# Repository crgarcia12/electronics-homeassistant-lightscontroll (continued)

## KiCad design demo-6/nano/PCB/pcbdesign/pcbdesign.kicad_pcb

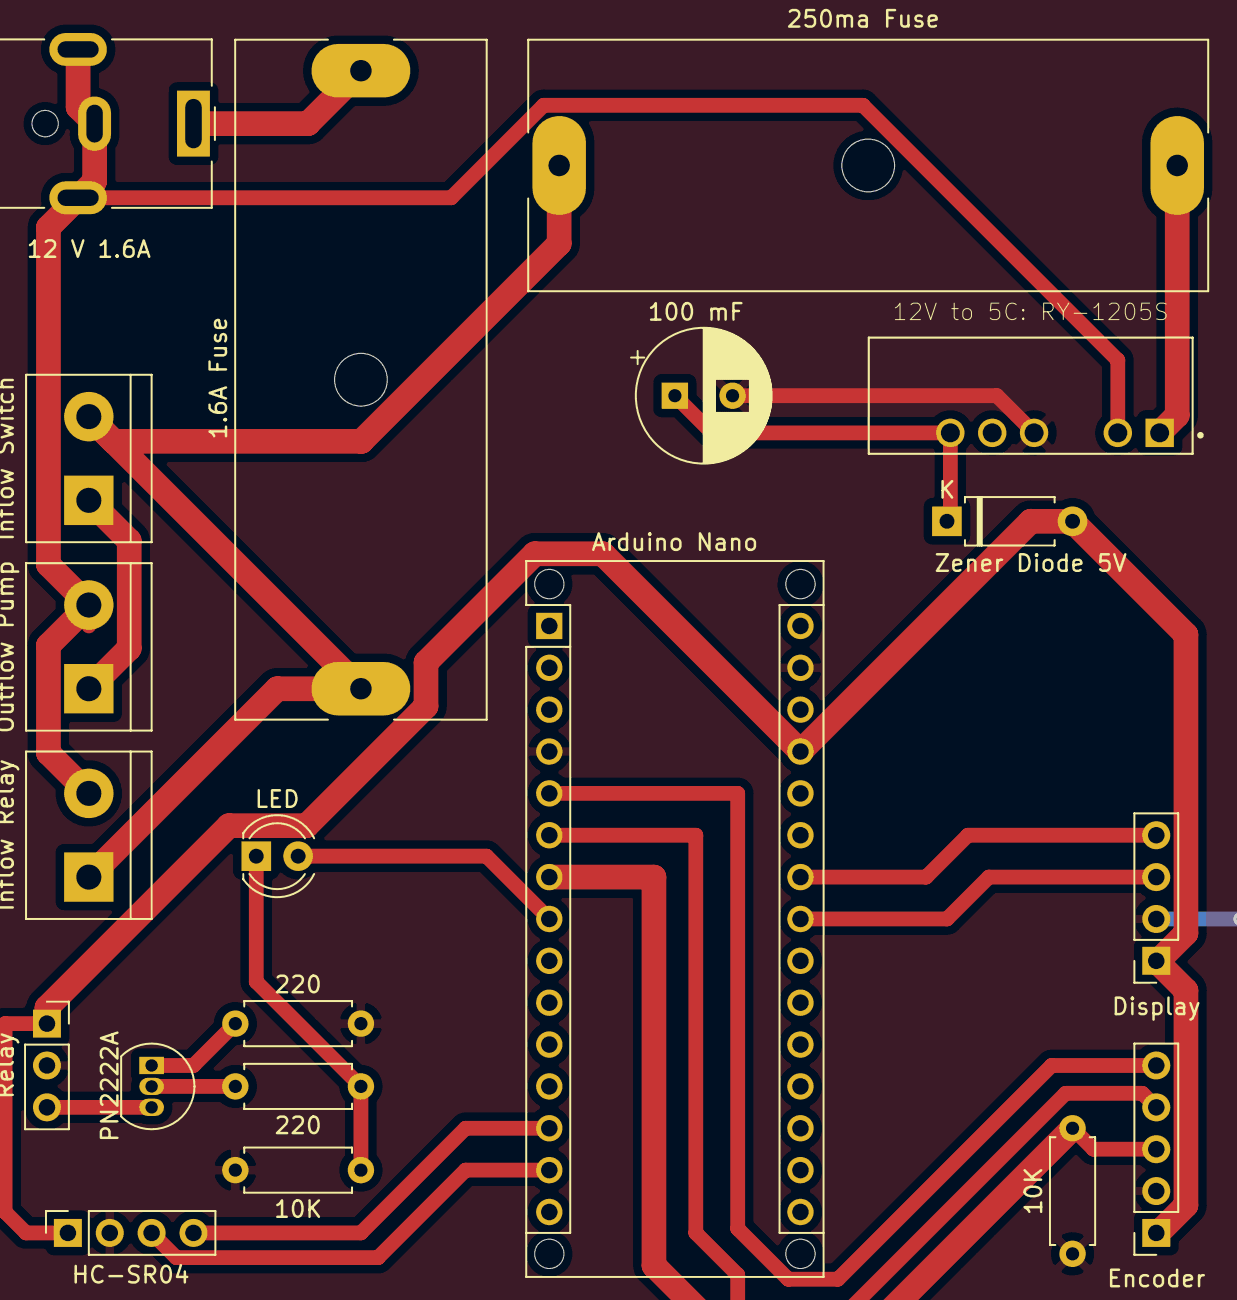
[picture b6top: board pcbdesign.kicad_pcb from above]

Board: 2 copper layers, 20 parts (0 on the bottom side), 20 nets.

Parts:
1.6A Fuse: 1.6A Fuse; Fuseholder_Cylinder-6.3x32mm_Schurter_0031-8002_Horizontal_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
10K, 10K#2: 10K; R_Axial_DIN0207_L6.3mm_D2.5mm_P7.62mm_Horizontal
12 V 1.6A: 12v input; BarrelJack_CUI_PJ-063AH_Horizontal
12V to 5C: RY-1205S: RY-1205S; CONV_RY-1205S
100 mF: 100 mF; CP_Radial_D8.0mm_P3.50mm
220, 220#2: 220; R_Axial_DIN0207_L6.3mm_D2.5mm_P7.62mm_Horizontal
250ma Fuse: 250ma Fuse; Fuseholder_Cylinder-6.3x32mm_Schurter_0031-8002_Horizontal_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
Arduino Nano: Arduino_Nano_v3.x; Arduino_Nano_WithMountingHoles
Display: Display; PinSocket_1x04_P2.54mm_Vertical
Encoder: Encoder; PinSocket_1x05_P2.54mm_Vertical
HC-SR04: HC-SR04; PinSocket_1x04_P2.54mm_Vertical
Inflow Relay: Inflow Relay; TerminalBlock_bornier-2_P5.08mm
Inflow Switch: Outflow Switch; TerminalBlock_bornier-2_P5.08mm
LED: LED; LED_D4.0mm
Outflow Pump: Outflow Pump; TerminalBlock_bornier-2_P5.08mm
PN2222A: PN2222A; TO-92_Inline
Relay: Relay; PinSocket_1x03_P2.54mm_Vertical
Zener Diode 5V: 5V; D_A-405_P7.62mm_Horizontal

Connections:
+5V: Arduino Nano.27, Display.1, Encoder.1, HC-SR04.1, Relay.1, Zener Diode 5V.2
GND: 10K.2, 10K#2.1, 12V to 5C: RY-1205S.4, 100 mF.2, 220#2.2, Arduino Nano.4, Arduino Nano.29, Display.2, Encoder.2, HC-SR04.2, Relay.2
unnamed: Arduino Nano.5, Encoder.5
unnamed: Arduino Nano.6, Encoder.4
unnamed: 10K#2.2, Arduino Nano.7, Encoder.3
unnamed: Arduino Nano.8, LED.2
unnamed: Arduino Nano.13, HC-SR04.4
unnamed: Arduino Nano.14, HC-SR04.3
unnamed: Arduino Nano.23, Display.3
unnamed: Arduino Nano.24, Display.4
unnamed: 12V to 5C: RY-1205S.6, 100 mF.1, Zener Diode 5V.1
unnamed: 10K.1, 220.1, LED.1
unnamed: 1.6A Fuse.1, 250ma Fuse.2, Inflow Relay.1, Inflow Switch.2
unnamed: 1.6A Fuse.2, 12 V 1.6A.1
unnamed: 12V to 5C: RY-1205S.1, 250ma Fuse.1
unnamed: PN2222A.3, Relay.3
unnamed: 12 V 1.6A.2, 12 V 1.6A.MP, 12V to 5C: RY-1205S.2, Inflow Relay.2, Outflow Pump.2
unnamed: Inflow Switch.1, Outflow Pump.1
unnamed: 220#2.1, PN2222A.1
unnamed: 220.2, PN2222A.2

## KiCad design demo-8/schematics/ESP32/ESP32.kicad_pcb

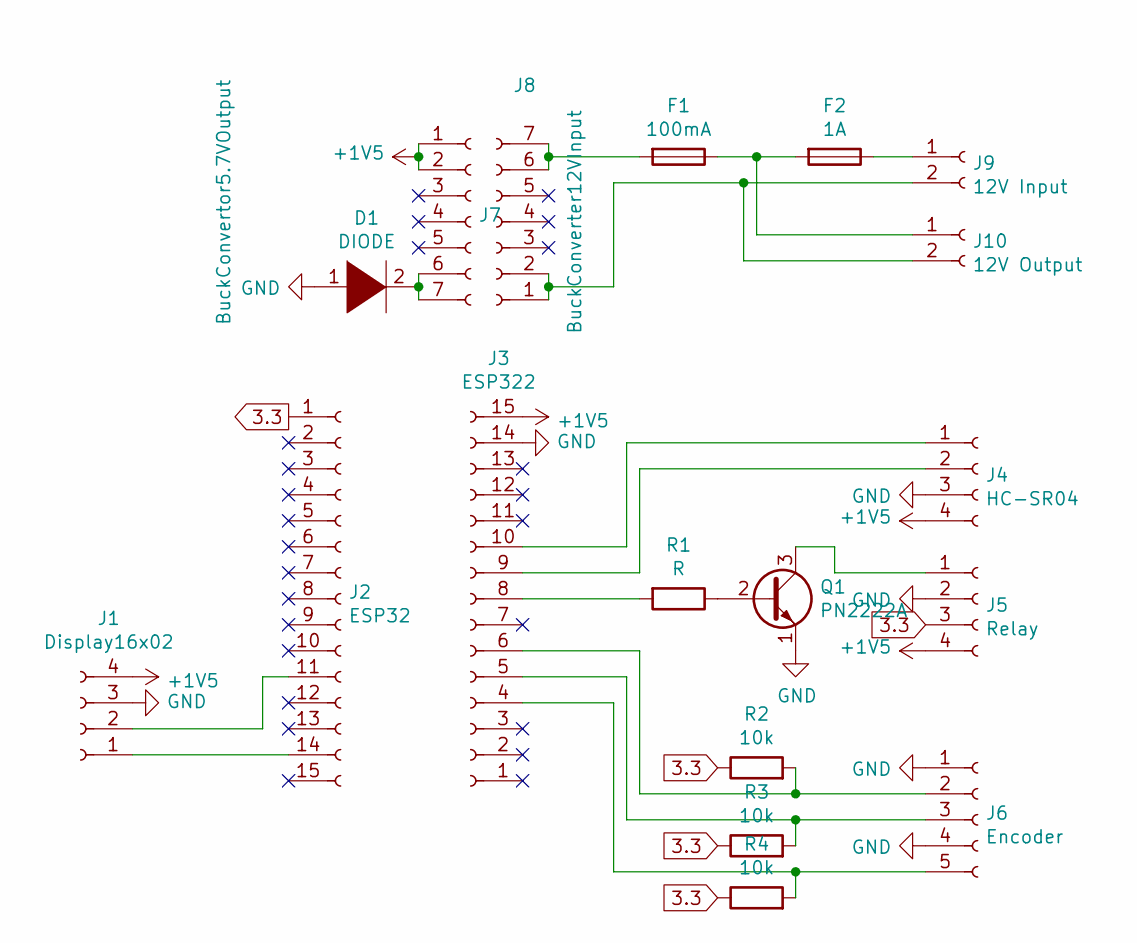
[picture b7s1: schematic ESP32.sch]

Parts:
D1: DIODE; D_5W_P12.70mm_Horizontal
F1: 100mA; Fuse_BelFuse_0ZRE0150FF_L23.4mm_W5.3mm
F2: 1A; Fuse_BelFuse_0ZRE0150FF_L23.4mm_W5.3mm
J1: Display16x02; PinSocket_1x04_P1.00mm_Vertical
J2: ESP32; PinSocket_1x15_P1.00mm_Vertical
J3: ESP322; PinSocket_1x15_P1.00mm_Vertical
J4: HC-SR04; PinSocket_1x04_P1.00mm_Vertical
J5: Relay; PinSocket_1x04_P1.00mm_Vertical
J6: Encoder; PinSocket_1x05_P1.00mm_Vertical
J7: BuckConvertor5.7VOutput; PinHeader_1x07_P1.00mm_Vertical
J8: BuckConverter12VInput; PinHeader_1x07_P1.00mm_Vertical
J9: 12V Input; PhoenixContact_GMSTBVA_2,5_2-G-7,62_1x02_P7.62mm_Vertical
J10: 12V Output; PhoenixContact_GMSTBVA_2,5_2-G-7,62_1x02_P7.62mm_Vertical
Q1: PN2222A; TO-92_Inline
R1: R; R_Axial_DIN0204_L3.6mm_D1.6mm_P5.08mm_Horizontal
R2, R3, R4: 10k; R_Axial_DIN0204_L3.6mm_D1.6mm_P5.08mm_Horizontal

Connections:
3.3: J2.1, J5.3, R2.1, R3.1, R4.1
+1V5: J1.4, J3.15, J4.4, J5.4, J7.1, J7.2
GND: D1.1 (K), J1.3, J3.14, J4.3, J5.2, J6.1, J6.4, Q1.1 (E)
unnamed: D1.2 (A), J7.6, J7.7
unnamed: F1.1, F2.2, J10.1
unnamed: F1.2, J8.6, J8.7
unnamed: F2.1, J9.1
unnamed: J1.1, J2.14
unnamed: J1.2, J2.11
unnamed: J3.4, J6.5, R4.2
unnamed: J3.5, J6.3, R3.2
unnamed: J3.6, J6.2, R2.2
unnamed: J3.8, R1.2
unnamed: J3.9, J4.2
unnamed: J3.10, J4.1
unnamed: J5.1, Q1.3 (C)
unnamed: J8.1, J8.2, J9.2, J10.2
unnamed: Q1.2 (B), R1.1

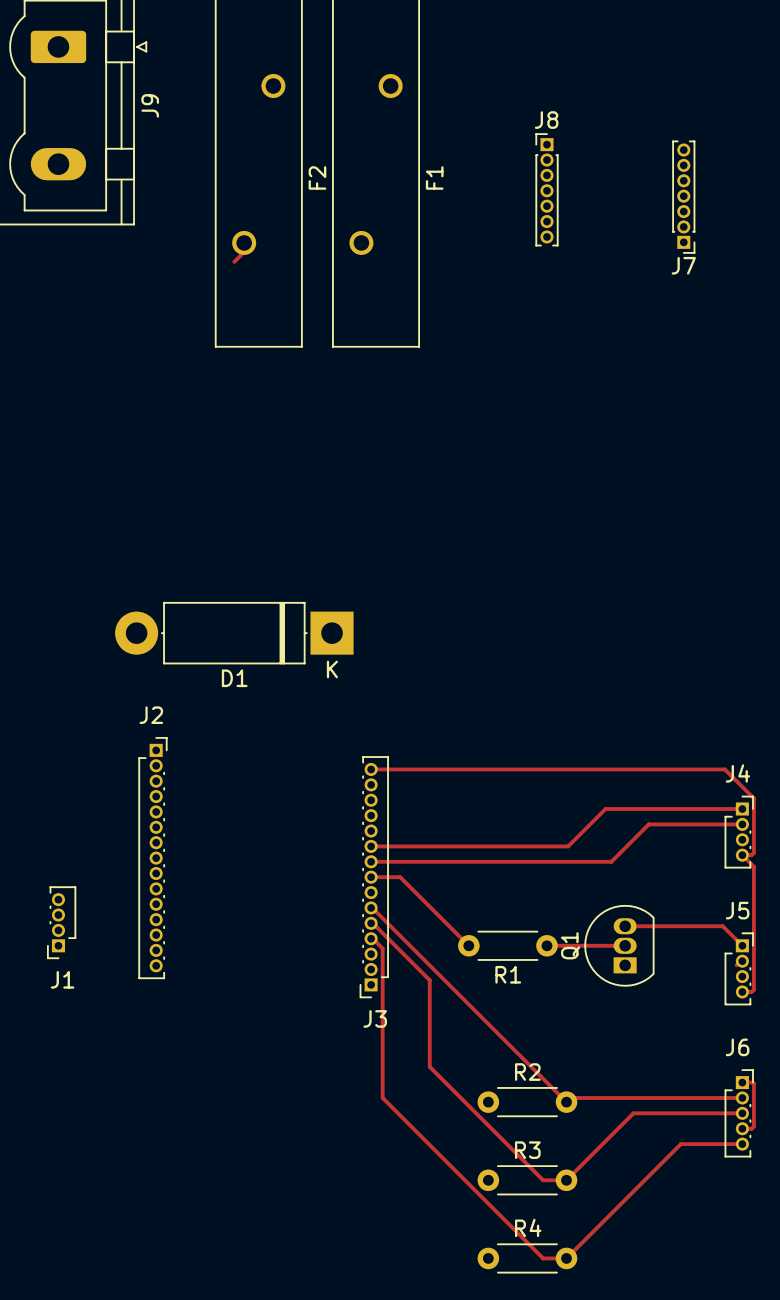
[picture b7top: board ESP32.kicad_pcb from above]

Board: 2 copper layers, 17 parts (0 on the bottom side), 18 nets.
